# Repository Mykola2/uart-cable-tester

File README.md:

# RPi ↔ CUAV X7 telemetry cable tester

A production tester for the harness that runs from a Raspberry Pi 40-pin header to 3× JST-GH 6-pin (CUAV X7 TELEM1–3). Plug a cable in and get a PASS/FAIL verdict in under a second, with a colour per wire:

| Colour | Meaning |
|---|---|
| green | OK |
| red | open |
| orange | miswired (swapped, wrong cavity, wrong pin) |
| magenta | short |

A wiggle test catches intermittent crimps.

## How it works
- **Test lines.** Every contact on the 40-pin header and on the three JSTs (58 lines) has its own MCP23017 I/O pin, through a 220 Ω resistor. The header's power and GND pins are isolated test lines too.
- **Scan.** The RP2040 drives one line low at a time and reads all the others (a "walking one" scan). That builds the full connection map, which it compares to `wiring.json`.
- **Changing the pinout** needs no new hardware. Either edit `wiring.json` on the board's USB drive, or plug in a known-good cable and hold the button for 3 s (learn mode).
- **Ground wires** may land on any Pi GND pin, because the Pi's grounds are common.

## Layout
| Path | Contents |
|---|---|
| `firmware/` | CircuitPython firmware and PC simulation tests. See [firmware/README.md](firmware/README.md). |
| `hardware/` | KiCad 9 project, generator and check scripts, BOM. See [hardware/README.md](hardware/README.md). |
| `hardware/fab/` | JLCPCB order files: Gerber zip, `BOM_JLC.csv`, `CPL_JLC.csv`. |

## Quick commands
```bash
python firmware/pc_tests/test_tester.py      # firmware logic tests
python hardware/check_design.py              # netlist vs firmware pin map
python hardware/make_jlc.py                  # regenerate JLCPCB files from the board
```

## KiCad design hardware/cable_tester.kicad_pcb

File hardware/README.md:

# Cable tester PCB (KiCad 9)

`design.py` is the single source of truth: parts, footprints, pin-to-net map and positions.
Everything else is generated from it.

| File | What it is |
|---|---|
| `cable_tester.kicad_sch` | Schematic. Every pin is connected by a net label; opens normally in KiCad. |
| `cable_tester.kicad_pcb` | Board, 135×90 mm, 2 layers. Routed with Freerouting, GND pours on both layers. DRC is clean apart from silkscreen warnings. |
| `BOM.csv` | Grouped BOM with MPNs. `fab/BOM_JLC.csv` has the verified LCSC numbers. |
| `fab/` | JLCPCB files (Gerber zip, BOM, CPL), regenerated by `make_jlc.py`. |
| `move_decoupling.py` | One-off fix already applied to the routed board: moved C1–C4 next to the MCP23017 VDD pins. |
| `cable_tester_schematic.pdf`, `render_top.png`, `render_bottom.png` | Previews of the schematic and the board. |

## Regenerate

```bash
python gen_schematic.py
"C:/Program Files/KiCad/9.0/bin/kicad-cli.exe" sch erc cable_tester.kicad_sch
"C:/Program Files/KiCad/9.0/bin/kicad-cli.exe" sch export netlist --format kicadsexpr -o cable_tester.net cable_tester.kicad_sch
python check_design.py
"C:/Program Files/KiCad/9.0/bin/python.exe" gen_pcb.py
```

`check_design.py` checks the exported netlist against `firmware/hwmap.py`:
- each of the 58 test lines runs connector pin → 220 Ω → the MCP23017 pin the firmware expects
- the address straps are correct
- no DUT pin touches a power net

**The board is routed, so don't run `gen_pcb.py` again**, because it overwrites the board.
After that, make changes in the schematic (or `design.py` followed by `gen_schematic.py`), then use *Tools → Update PCB from Schematic* (F8).

## Circuit summary
- **A1**: Raspberry Pi Pico or a WeAct RP2040 (USB-C, same pinout).
  - USB supplies VBUS (+5 V), which powers the LEDs and buzzer.
  - The module's 3V3 output powers the MCP23017s.
  - Pins used: GP4 SDA, GP5 SCL, GP14 buzzer, GP15 button, GP16 LED data.
- **U1–U4**: MCP23017 at I²C addresses 0x20–0x23. Every DUT contact goes to its own expander pin through one resistor in RN1–RN15 (4×220 Ω arrays).
  - U1: H1–16. U2: H17–32. U3: GPA = H33–40, GPB0–5 = TELEM1.
  - U4: GPA0–5 = TELEM2, GPB0–5 = TELEM3.
  - Spare lines: U3 GPB6–7, U4 GPA6–7, U4 GPB6–7.
- **J1**: the 40-pin header. **None of its pins touch GND, 3V3 or 5V.** Each one is an isolated test line, which is why any future pinout can be tested with a config change only.
- **D1–D10**: WS2812B, driven through U5 (74AHCT1G125) to shift the data line from 3.3 V to 5 V.
  - D1–D9 are the wire LEDs: TX / RX / GND for each TELEM connector.
  - D10 is the PASS/FAIL status LED.
- **BZ1**: 5 V active buzzer, switched by Q1 with flyback diode D11.
- **SW1**: START / LEARN button.
- **J5**: optional SSD1306 OLED header. The firmware doesn't drive it yet.

## Before ordering
1. **Route it.** Freerouting works well:
   - export with *File → Export → Specctra DSN*, route in Freerouting, then import the `.ses` file
   - press **B** to fill the GND pours
   - run DRC
2. **Check JST orientation in the 3D viewer (Alt+3).** The TELEM connectors must open toward the bottom board edge.
3. **Check the header orientation.** It copies a Pi seen from above: pin 1 is bottom-left on the silkscreen, and the even-pin row is along the board edge. The cable must plug in exactly as it does on the Pi.
4. **Check the module footprint.** If you use a Pico clone, confirm it matches `RaspberryPi_Pico_SMD_HandSolder`.
5. **JST-GH receptacles are consumables.** They are rated for only ~50 mating cycles. Order spares and replace them with hot air when mating gets loose.

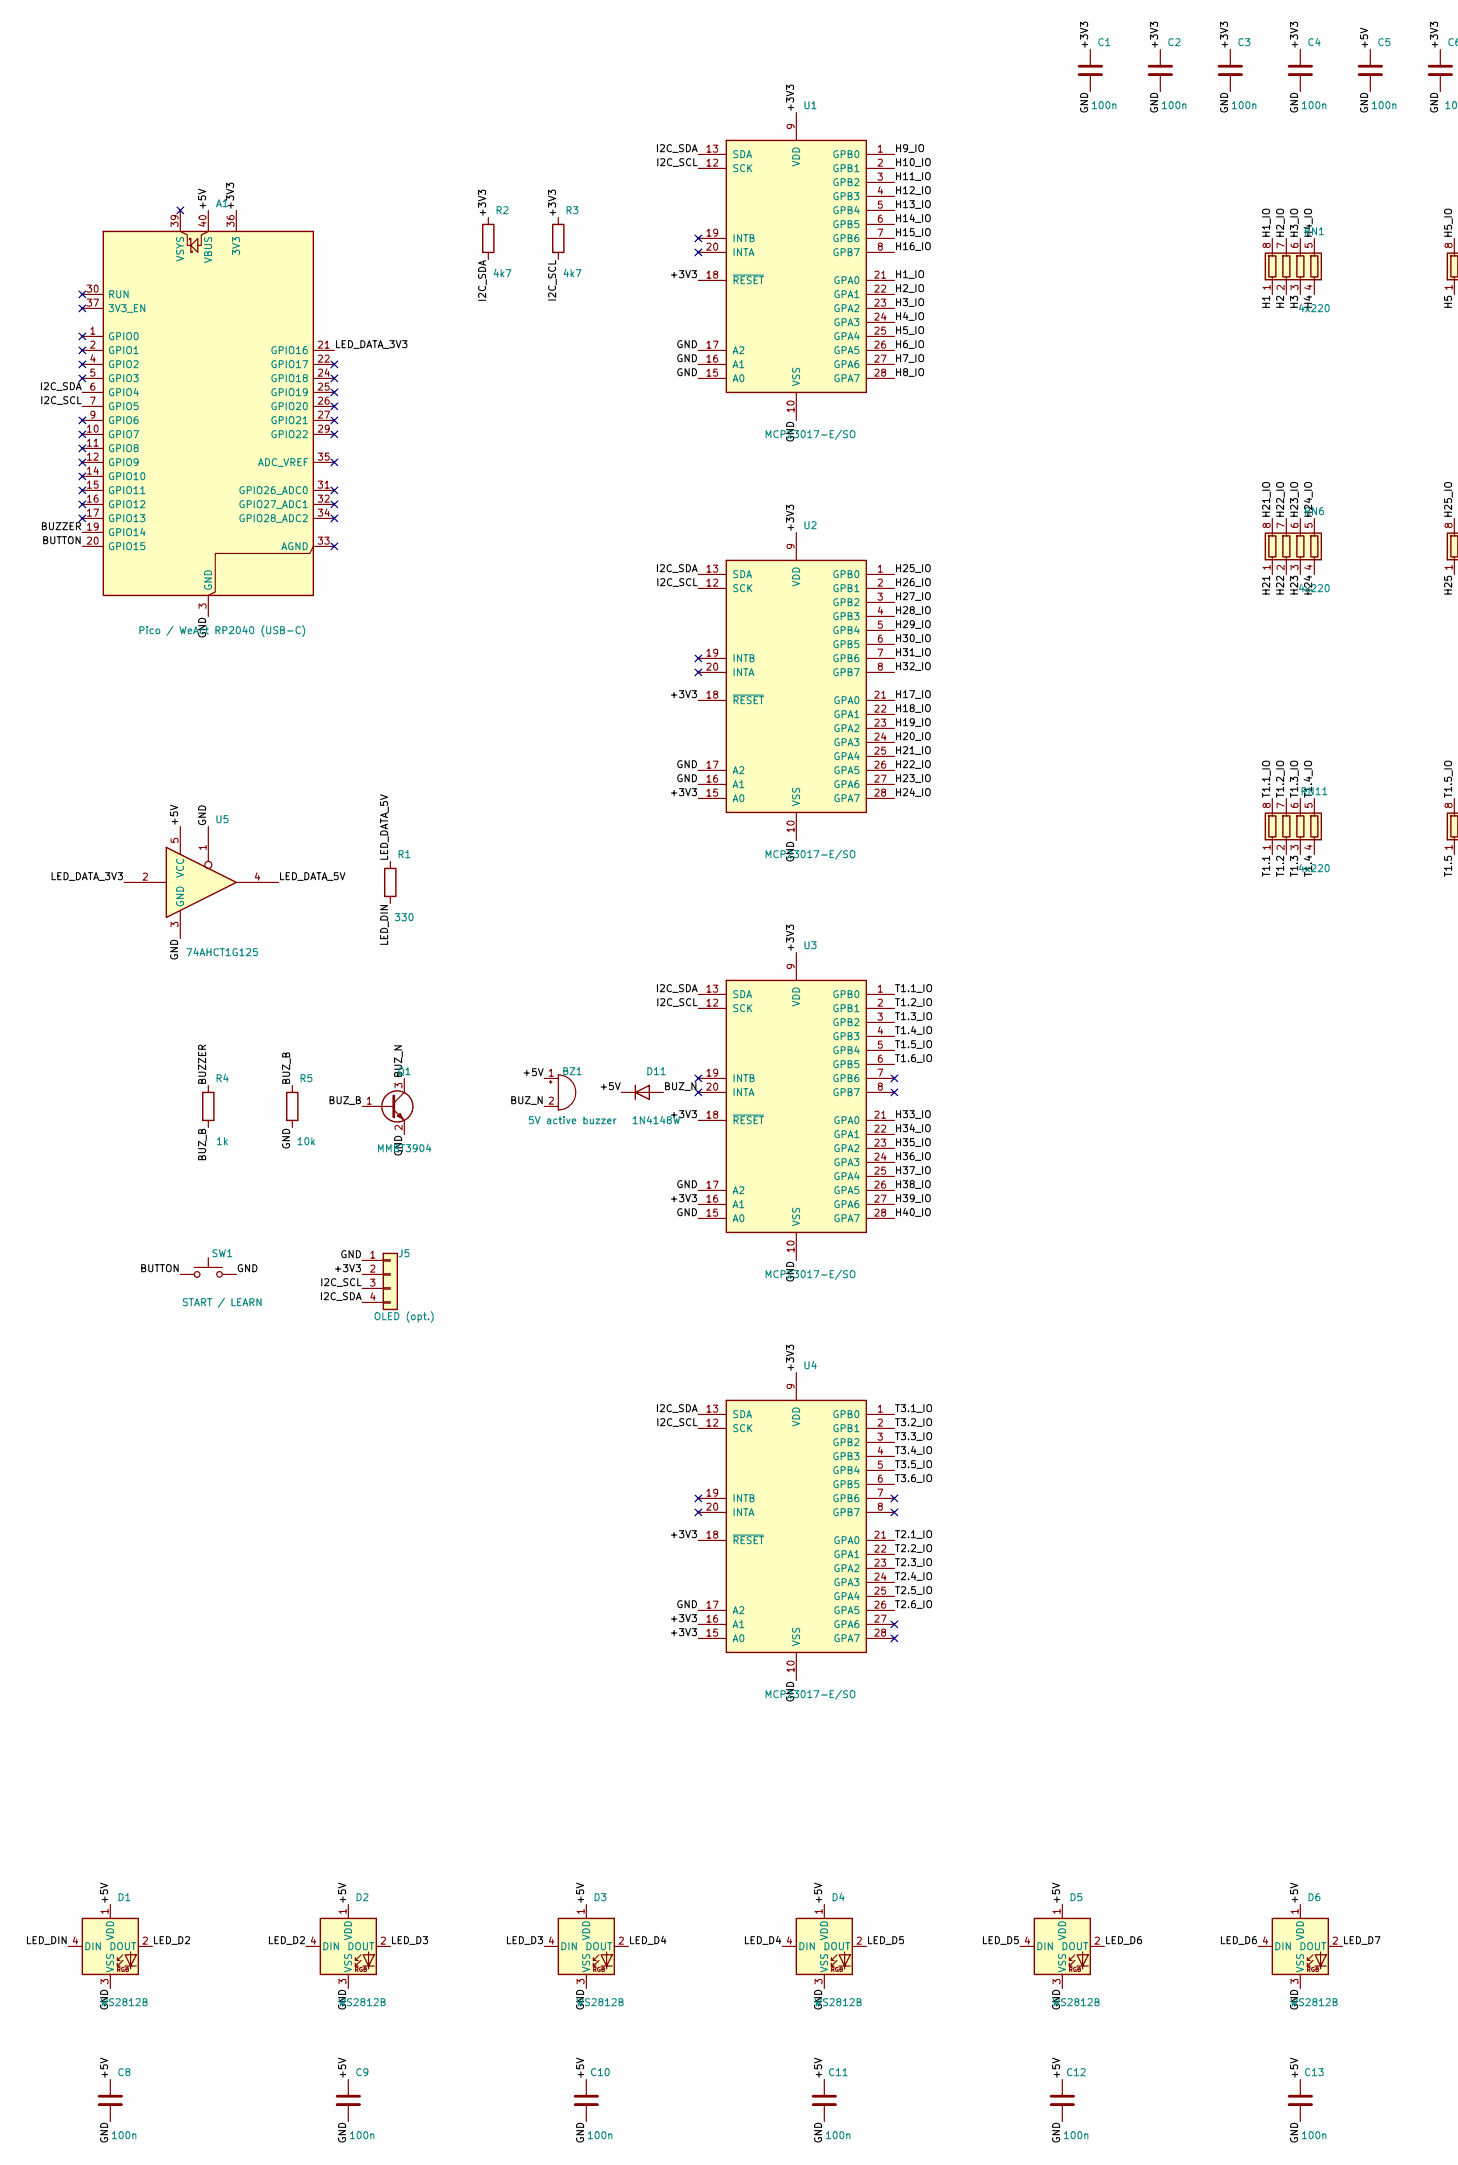
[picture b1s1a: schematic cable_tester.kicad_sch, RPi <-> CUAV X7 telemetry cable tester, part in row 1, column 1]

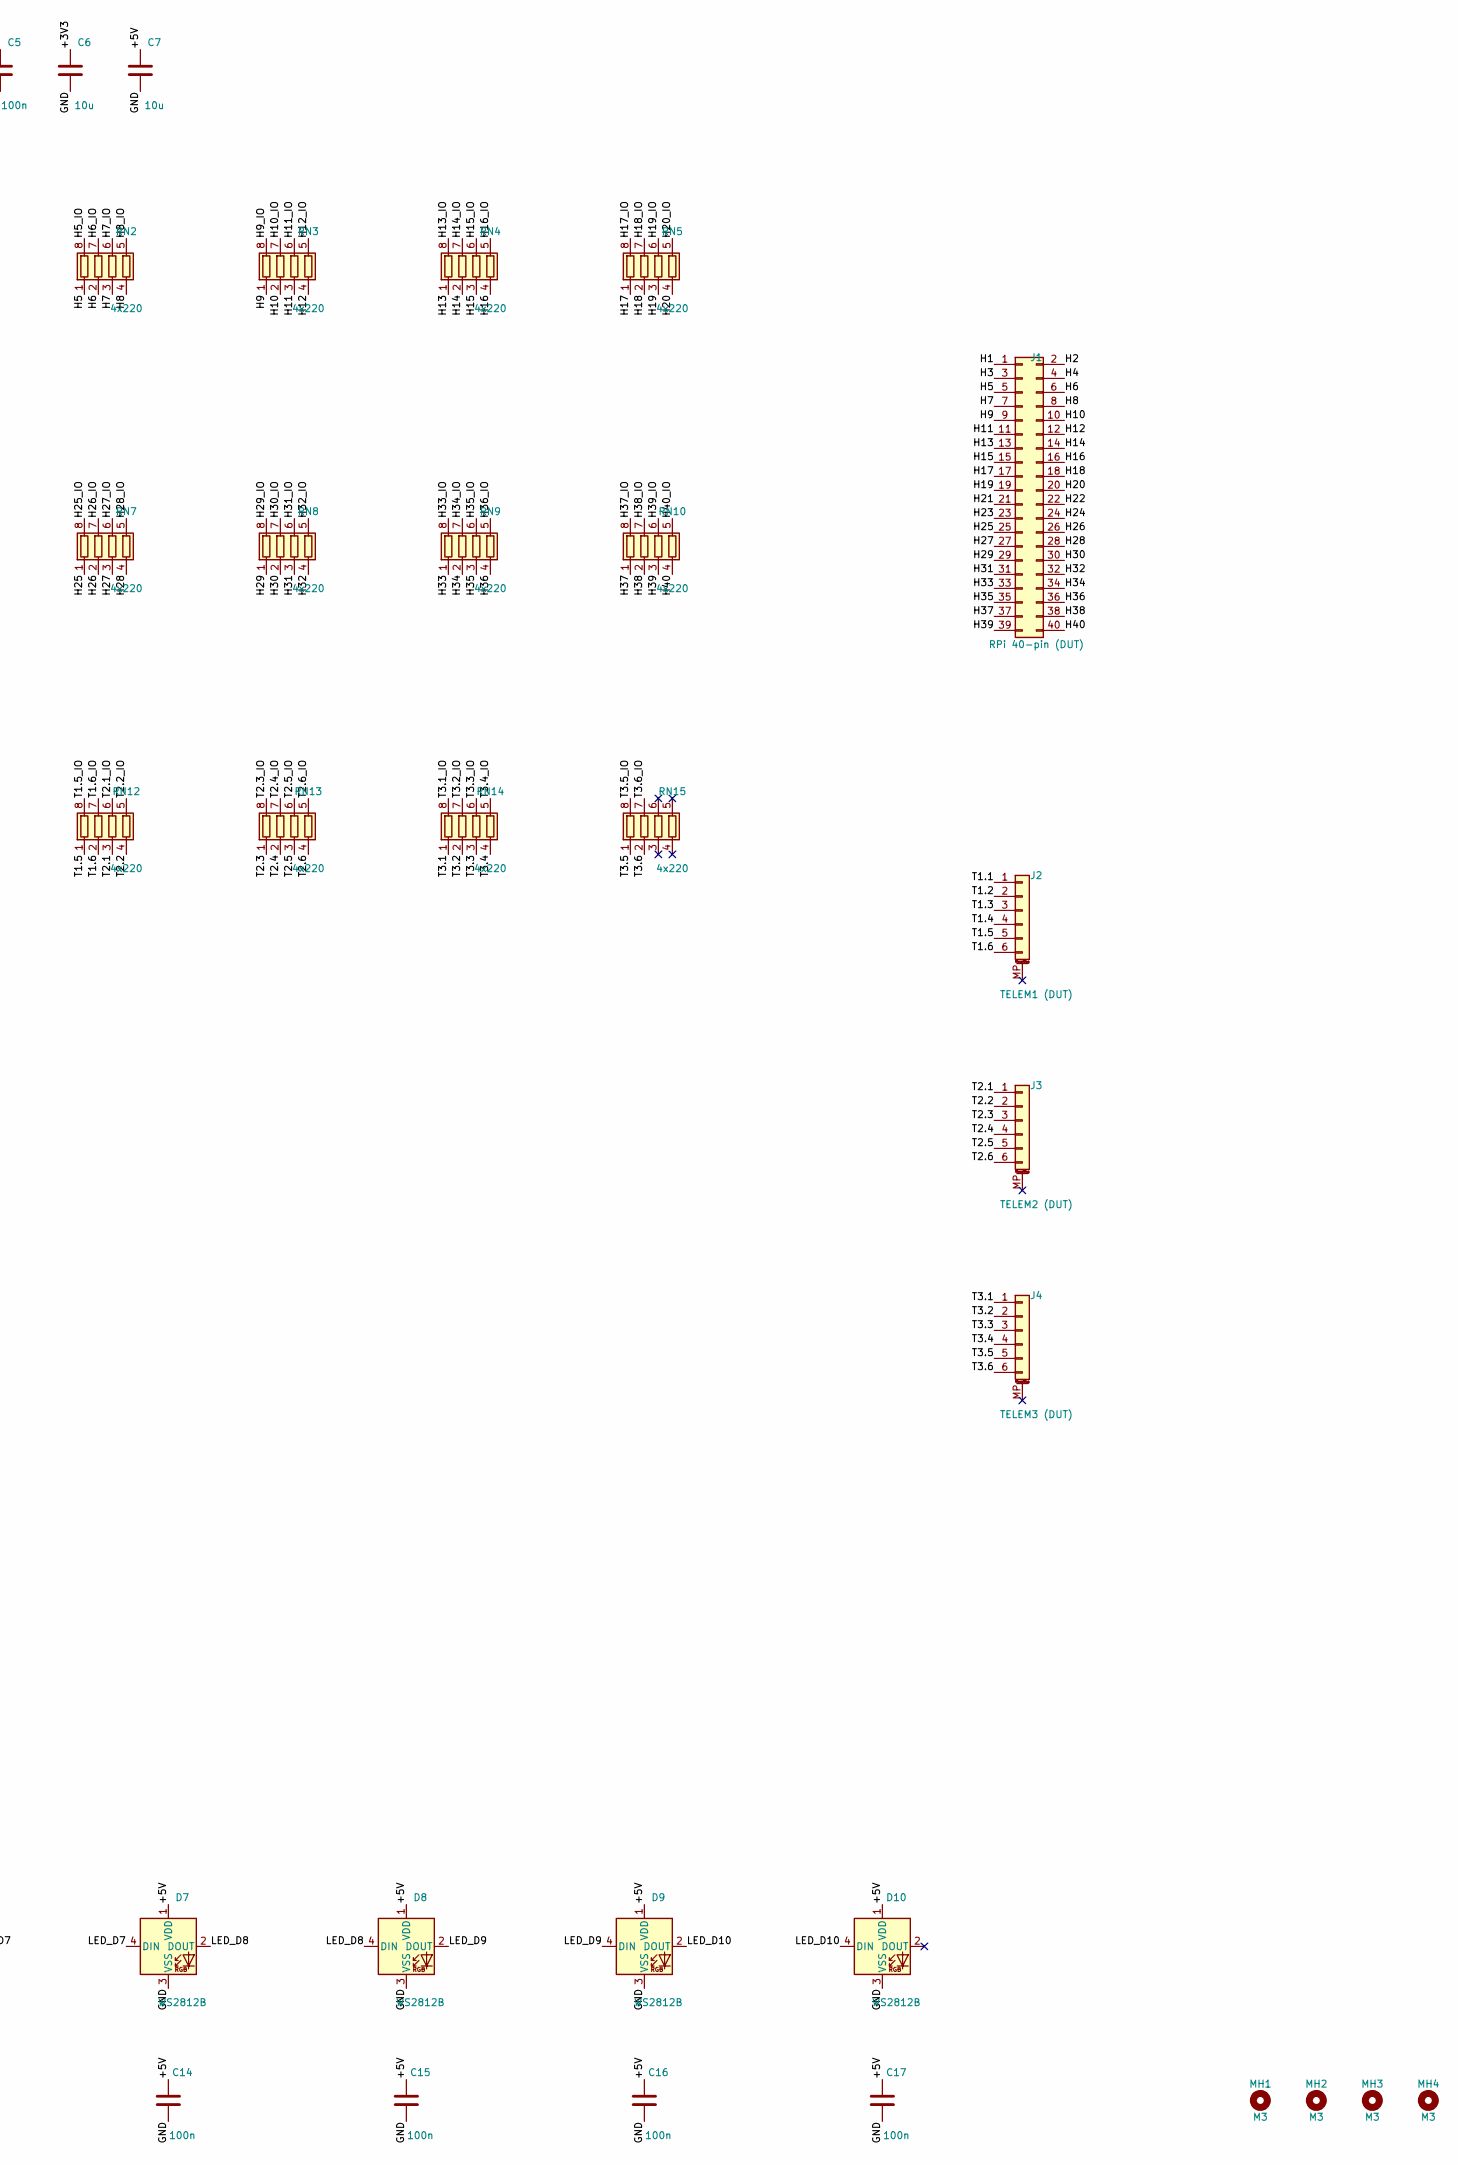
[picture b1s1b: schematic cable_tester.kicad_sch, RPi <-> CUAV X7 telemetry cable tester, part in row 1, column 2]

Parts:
A1: Pico / WeAct RP2040 (USB-C); RaspberryPi_Pico_SMD_HandSolder; MPN Raspberry Pi Pico (SC0915) or WeAct Stu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
BZ1: 5V active buzzer; Buzzer_12x9.5RM7.6; MPN TMB12A05 (12mm 5V active, 7.6mm pitch)
C1, C2, C3, C4, C5, C8, C9, C10, C11, C12, C13, C14, C15, C16, C17: 100n; C_0603_1608Metric; MPN 0603 100nF X7R 16V
C6, C7: 10u; C_0805_2012Metric; MPN 0805 10uF X5R 16V
D1, D2, D3, D4, D5, D6, D7, D8, D9, D10: WS2812B; LED_WS2812B_PLCC4_5.0x5.0mm_P3.2mm; MPN WS2812B-5050
D11: 1N4148W; D_SOD-123; MPN 1N4148W
J1: RPi 40-pin (DUT); PinHeader_2x20_P2.54mm_Vertical; MPN 2x20 2.54mm male pin header
J2: TELEM1 (DUT); JST_GH_SM06B-GHS-TB_1x06-1MP_P1.25mm_Horizontal; MPN JST SM06B-GHS-TB(LF)(SN)
J3: TELEM2 (DUT); JST_GH_SM06B-GHS-TB_1x06-1MP_P1.25mm_Horizontal; MPN JST SM06B-GHS-TB(LF)(SN)
J4: TELEM3 (DUT); JST_GH_SM06B-GHS-TB_1x06-1MP_P1.25mm_Horizontal; MPN JST SM06B-GHS-TB(LF)(SN)
J5: OLED (opt.); PinHeader_1x04_P2.54mm_Vertical; MPN 1x4 2.54mm header (DNP)
MH1, MH2, MH3, MH4: M3; MountingHole_3.2mm_M3; MPN (none)
Q1: MMBT3904; SOT-23; MPN MMBT3904
R1: 330; R_0603_1608Metric; MPN 0603 330R
R2, R3: 4k7; R_0603_1608Metric; MPN 0603 4.7k
R4: 1k; R_0603_1608Metric; MPN 0603 1k
R5: 10k; R_0603_1608Metric; MPN 0603 10k
RN1, RN2, RN3, RN4, RN5, RN6, RN7, RN8, RN9, RN10, RN11, RN12, RN13, RN14, RN15: 4x220; R_Array_Convex_4x0603; MPN YC164-JR-07220RL (4x220R 0603 convex)
SW1: START / LEARN; SW_PUSH_6mm_H5mm; MPN 6x6mm THT tactile switch
U1, U2, U3, U4: MCP23017-E/SO; SOIC-28W_7.5x17.9mm_P1.27mm; MPN MCP23017-E/SO
U5: 74AHCT1G125; SOT-23-5; MPN SN74AHCT1G125DBVR

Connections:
/+3V3: A1.36 (3V3), C1.1, C2.1, C3.1, C4.1, C6.1, J5.2, R2.1, R3.1, U1.9 (VDD), U1.18 (~RESET), U2.9 (VDD), U2.15 (A0), U2.18 (~RESET), U3.9 (VDD), U3.16 (A1), U3.18 (~RESET), U4.9 (VDD), U4.15 (A0), U4.16 (A1), U4.18 (~RESET)
/+5V: A1.40 (VBUS), BZ1.1 (+), C5.1, C7.1, C8.1, C9.1, C10.1, C11.1, C12.1, C13.1, C14.1, C15.1, C16.1, C17.1, D1.1 (VDD), D2.1 (VDD), D3.1 (VDD), D4.1 (VDD), D5.1 (VDD), D6.1 (VDD), D7.1 (VDD), D8.1 (VDD), D9.1 (VDD), D10.1 (VDD), D11.1 (K), U5.5 (VCC)
/BUTTON: A1.20 (GPIO15), SW1.1
/BUZZER: A1.19 (GPIO14), R4.1
/BUZ_B: Q1.1 (B), R4.2, R5.1
/BUZ_N: BZ1.2 (-), D11.2 (A), Q1.3 (C)
/GND: A1.3 (GND), A1.8 (GND), A1.13 (GND), A1.18 (GND), A1.23 (GND), A1.28 (GND), A1.38 (GND), C1.2, C2.2, C3.2, C4.2, C5.2, C6.2, C7.2, C8.2, C9.2, C10.2, C11.2, C12.2, C13.2, C14.2, C15.2, C16.2, C17.2, D1.3 (VSS), D2.3 (VSS), D3.3 (VSS), D4.3 (VSS), D5.3 (VSS), D6.3 (VSS), D7.3 (VSS), D8.3 (VSS), D9.3 (VSS), D10.3 (VSS), J5.1, Q1.2 (E), R5.2, SW1.2, U1.10 (VSS), U1.15 (A0), U1.16 (A1), U1.17 (A2), U2.10 (VSS), U2.16 (A1), U2.17 (A2), U3.10 (VSS), U3.15 (A0), U3.17 (A2), U4.10 (VSS), U4.17 (A2), U5.1, U5.3 (GND)
/H1: J1.1, RN1.1 (R1.1)
/H1_IO: RN1.8 (R1.2), U1.21 (GPA0)
/H2: J1.2, RN1.2 (R2.1)
/H2_IO: RN1.7 (R2.2), U1.22 (GPA1)
/H3: J1.3, RN1.3 (R3.1)
/H3_IO: RN1.6 (R3.2), U1.23 (GPA2)
/H4: J1.4, RN1.4 (R4.1)
/H4_IO: RN1.5 (R4.2), U1.24 (GPA3)
/H5: J1.5, RN2.1 (R1.1)
/H5_IO: RN2.8 (R1.2), U1.25 (GPA4)
/H6: J1.6, RN2.2 (R2.1)
/H6_IO: RN2.7 (R2.2), U1.26 (GPA5)
/H7: J1.7, RN2.3 (R3.1)
/H7_IO: RN2.6 (R3.2), U1.27 (GPA6)
/H8: J1.8, RN2.4 (R4.1)
/H8_IO: RN2.5 (R4.2), U1.28 (GPA7)
/H9: J1.9, RN3.1 (R1.1)
/H9_IO: RN3.8 (R1.2), U1.1 (GPB0)
/H10: J1.10, RN3.2 (R2.1)
/H10_IO: RN3.7 (R2.2), U1.2 (GPB1)
/H11: J1.11, RN3.3 (R3.1)
/H11_IO: RN3.6 (R3.2), U1.3 (GPB2)
/H12: J1.12, RN3.4 (R4.1)
/H12_IO: RN3.5 (R4.2), U1.4 (GPB3)
/H13: J1.13, RN4.1 (R1.1)
/H13_IO: RN4.8 (R1.2), U1.5 (GPB4)
/H14: J1.14, RN4.2 (R2.1)
/H14_IO: RN4.7 (R2.2), U1.6 (GPB5)
/H15: J1.15, RN4.3 (R3.1)
/H15_IO: RN4.6 (R3.2), U1.7 (GPB6)
/H16: J1.16, RN4.4 (R4.1)
/H16_IO: RN4.5 (R4.2), U1.8 (GPB7)
/H17: J1.17, RN5.1 (R1.1)
/H17_IO: RN5.8 (R1.2), U2.21 (GPA0)
/H18: J1.18, RN5.2 (R2.1)
/H18_IO: RN5.7 (R2.2), U2.22 (GPA1)
/H19: J1.19, RN5.3 (R3.1)
/H19_IO: RN5.6 (R3.2), U2.23 (GPA2)
/H20: J1.20, RN5.4 (R4.1)
/H20_IO: RN5.5 (R4.2), U2.24 (GPA3)
/H21: J1.21, RN6.1 (R1.1)
/H21_IO: RN6.8 (R1.2), U2.25 (GPA4)
/H22: J1.22, RN6.2 (R2.1)
/H22_IO: RN6.7 (R2.2), U2.26 (GPA5)
/H23: J1.23, RN6.3 (R3.1)
/H23_IO: RN6.6 (R3.2), U2.27 (GPA6)
/H24: J1.24, RN6.4 (R4.1)
/H24_IO: RN6.5 (R4.2), U2.28 (GPA7)
/H25: J1.25, RN7.1 (R1.1)
/H25_IO: RN7.8 (R1.2), U2.1 (GPB0)
/H26: J1.26, RN7.2 (R2.1)
/H26_IO: RN7.7 (R2.2), U2.2 (GPB1)
/H27: J1.27, RN7.3 (R3.1)
/H27_IO: RN7.6 (R3.2), U2.3 (GPB2)
/H28: J1.28, RN7.4 (R4.1)
/H28_IO: RN7.5 (R4.2), U2.4 (GPB3)
/H29: J1.29, RN8.1 (R1.1)
/H29_IO: RN8.8 (R1.2), U2.5 (GPB4)
/H30: J1.30, RN8.2 (R2.1)
/H30_IO: RN8.7 (R2.2), U2.6 (GPB5)
/H31: J1.31, RN8.3 (R3.1)
/H31_IO: RN8.6 (R3.2), U2.7 (GPB6)
/H32: J1.32, RN8.4 (R4.1)
/H32_IO: RN8.5 (R4.2), U2.8 (GPB7)
/H33: J1.33, RN9.1 (R1.1)
/H33_IO: RN9.8 (R1.2), U3.21 (GPA0)
/H34: J1.34, RN9.2 (R2.1)
/H34_IO: RN9.7 (R2.2), U3.22 (GPA1)
/H35: J1.35, RN9.3 (R3.1)
/H35_IO: RN9.6 (R3.2), U3.23 (GPA2)
/H36: J1.36, RN9.4 (R4.1)
/H36_IO: RN9.5 (R4.2), U3.24 (GPA3)
/H37: J1.37, RN10.1 (R1.1)
/H37_IO: RN10.8 (R1.2), U3.25 (GPA4)
/H38: J1.38, RN10.2 (R2.1)
/H38_IO: RN10.7 (R2.2), U3.26 (GPA5)
/H39: J1.39, RN10.3 (R3.1)
/H39_IO: RN10.6 (R3.2), U3.27 (GPA6)
/H40: J1.40, RN10.4 (R4.1)
/H40_IO: RN10.5 (R4.2), U3.28 (GPA7)
/I2C_SCL: A1.7 (GPIO5), J5.3, R3.2, U1.12 (SCK), U2.12 (SCK), U3.12 (SCK), U4.12 (SCK)
/I2C_SDA: A1.6 (GPIO4), J5.4, R2.2, U1.13 (SDA), U2.13 (SDA), U3.13 (SDA), U4.13 (SDA)
/LED_D2: D1.2 (DOUT), D2.4 (DIN)
/LED_D3: D2.2 (DOUT), D3.4 (DIN)
/LED_D4: D3.2 (DOUT), D4.4 (DIN)
/LED_D5: D4.2 (DOUT), D5.4 (DIN)
/LED_D6: D5.2 (DOUT), D6.4 (DIN)
/LED_D7: D6.2 (DOUT), D7.4 (DIN)
/LED_D8: D7.2 (DOUT), D8.4 (DIN)
/LED_D9: D8.2 (DOUT), D9.4 (DIN)
/LED_D10: D9.2 (DOUT), D10.4 (DIN)
/LED_DATA_3V3: A1.21 (GPIO16), U5.2
/LED_DATA_5V: R1.1, U5.4
/LED_DIN: D1.4 (DIN), R1.2
/T1.1: J2.1, RN11.1 (R1.1)
/T1.1_IO: RN11.8 (R1.2), U3.1 (GPB0)
/T1.2: J2.2, RN11.2 (R2.1)
/T1.2_IO: RN11.7 (R2.2), U3.2 (GPB1)
/T1.3: J2.3, RN11.3 (R3.1)
/T1.3_IO: RN11.6 (R3.2), U3.3 (GPB2)
/T1.4: J2.4, RN11.4 (R4.1)
/T1.4_IO: RN11.5 (R4.2), U3.4 (GPB3)
/T1.5: J2.5, RN12.1 (R1.1)
/T1.5_IO: RN12.8 (R1.2), U3.5 (GPB4)
/T1.6: J2.6, RN12.2 (R2.1)
/T1.6_IO: RN12.7 (R2.2), U3.6 (GPB5)
/T2.1: J3.1, RN12.3 (R3.1)
/T2.1_IO: RN12.6 (R3.2), U4.21 (GPA0)
/T2.2: J3.2, RN12.4 (R4.1)
/T2.2_IO: RN12.5 (R4.2), U4.22 (GPA1)
/T2.3: J3.3, RN13.1 (R1.1)
/T2.3_IO: RN13.8 (R1.2), U4.23 (GPA2)
/T2.4: J3.4, RN13.2 (R2.1)
/T2.4_IO: RN13.7 (R2.2), U4.24 (GPA3)
/T2.5: J3.5, RN13.3 (R3.1)
/T2.5_IO: RN13.6 (R3.2), U4.25 (GPA4)
/T2.6: J3.6, RN13.4 (R4.1)
/T2.6_IO: RN13.5 (R4.2), U4.26 (GPA5)
/T3.1: J4.1, RN14.1 (R1.1)
/T3.1_IO: RN14.8 (R1.2), U4.1 (GPB0)
/T3.2: J4.2, RN14.2 (R2.1)
/T3.2_IO: RN14.7 (R2.2), U4.2 (GPB1)
/T3.3: J4.3, RN14.3 (R3.1)
/T3.3_IO: RN14.6 (R3.2), U4.3 (GPB2)
/T3.4: J4.4, RN14.4 (R4.1)
/T3.4_IO: RN14.5 (R4.2), U4.4 (GPB3)
/T3.5: J4.5, RN15.1 (R1.1)
/T3.5_IO: RN15.8 (R1.2), U4.5 (GPB4)
/T3.6: J4.6, RN15.2 (R2.1)
/T3.6_IO: RN15.7 (R2.2), U4.6 (GPB5)

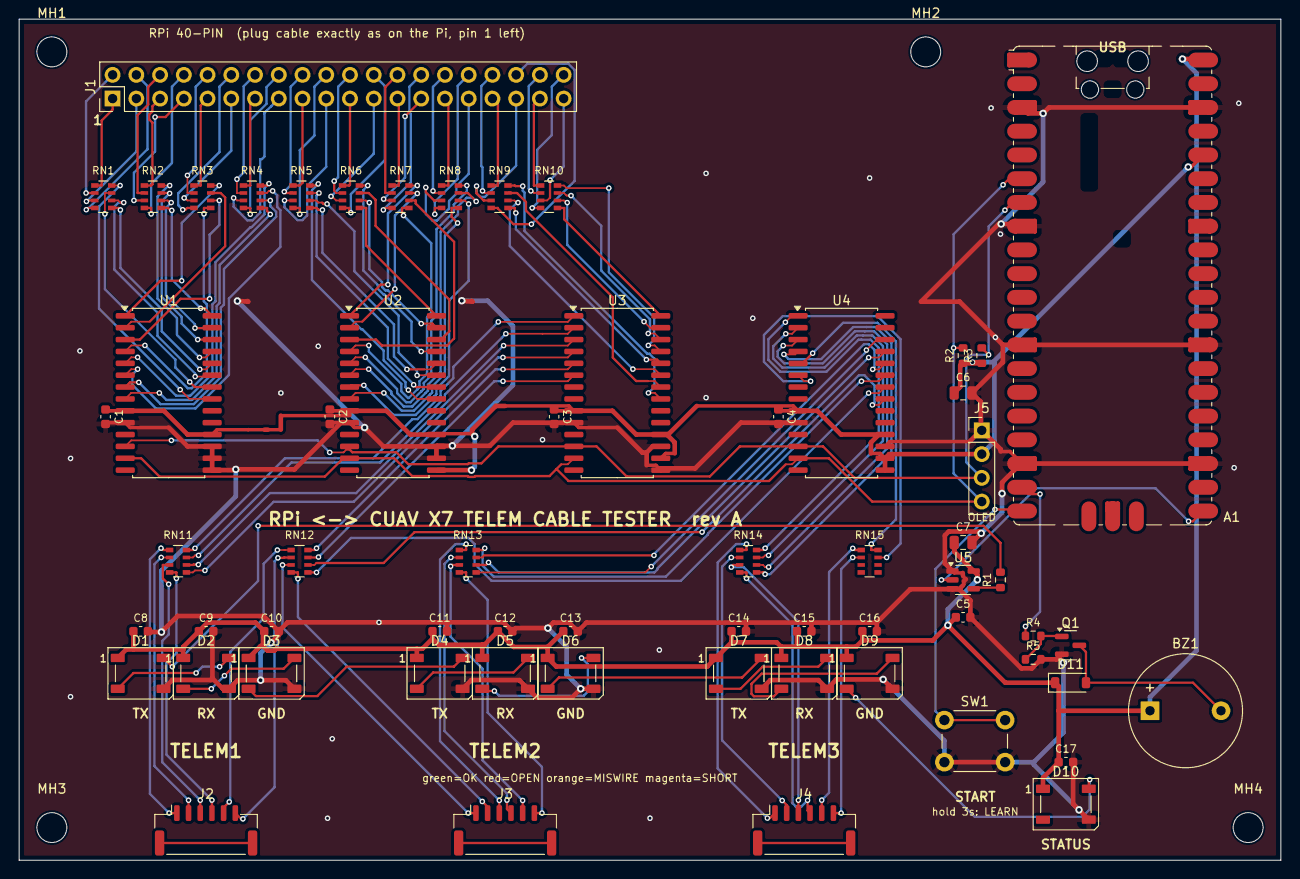
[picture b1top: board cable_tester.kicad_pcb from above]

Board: 2 copper layers, 135.0 x 90.0 mm, 66 parts (0 on the bottom side), 137 nets.

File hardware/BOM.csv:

Qty,References,Value,Footprint,MPN,LCSC (fill in),Notes
1,"A1","Pico / WeAct RP2040 (USB-C)","Module:RaspberryPi_Pico_SMD_HandSolder","Raspberry Pi Pico (SC0915) or WeAct Studio RP2040",,"USB-C variant recommended; castellated, solder directly or on 2x 1x20 sockets"
1,"BZ1","5V active buzzer","Buzzer_Beeper:Buzzer_12x9.5RM7.6","TMB12A05 (12mm 5V active, 7.6mm pitch)",,""
15,"C1 C2 C3 C4 C5 C8 C9 C10 C11 C12 C13 C14 C15 C16 C17","100n","Capacitor_SMD:C_0603_1608Metric","0603 100nF X7R 16V",,""
2,"C6 C7","10u","Capacitor_SMD:C_0805_2012Metric","0805 10uF X5R 16V",,""
10,"D1 D2 D3 D4 D5 D6 D7 D8 D9 D10","WS2812B","LED_SMD:LED_WS2812B_PLCC4_5.0x5.0mm_P3.2mm","WS2812B-5050",,""
1,"D11","1N4148W","Diode_SMD:D_SOD-123","1N4148W",,""
1,"J1","RPi 40-pin (DUT)","Connector_PinHeader_2.54mm:PinHeader_2x20_P2.54mm_Vertical","2x20 2.54mm male pin header",,"ALL pins are isolated test lines - never tie to power/GND"
1,"J2","TELEM1 (DUT)","Connector_JST:JST_GH_SM06B-GHS-TB_1x06-1MP_P1.25mm_Horizontal","JST SM06B-GHS-TB(LF)(SN)",,"~50 mating cycles: consumable, keep spares"
1,"J3","TELEM2 (DUT)","Connector_JST:JST_GH_SM06B-GHS-TB_1x06-1MP_P1.25mm_Horizontal","JST SM06B-GHS-TB(LF)(SN)",,"~50 mating cycles: consumable, keep spares"
1,"J4","TELEM3 (DUT)","Connector_JST:JST_GH_SM06B-GHS-TB_1x06-1MP_P1.25mm_Horizontal","JST SM06B-GHS-TB(LF)(SN)",,"~50 mating cycles: consumable, keep spares"
1,"J5","OLED (opt.)","Connector_PinHeader_2.54mm:PinHeader_1x04_P2.54mm_Vertical","1x4 2.54mm header (DNP)",,"SSD1306 128x64 I2C, GND-VCC-SCL-SDA"
1,"Q1","MMBT3904","Package_TO_SOT_SMD:SOT-23","MMBT3904",,""
1,"R1","330","Resistor_SMD:R_0603_1608Metric","0603 330R",,""
2,"R2 R3","4k7","Resistor_SMD:R_0603_1608Metric","0603 4.7k",,""
1,"R4","1k","Resistor_SMD:R_0603_1608Metric","0603 1k",,""
1,"R5","10k","Resistor_SMD:R_0603_1608Metric","0603 10k",,""
15,"RN1 RN2 RN3 RN4 RN5 RN6 RN7 RN8 RN9 RN10 RN11 RN12 RN13 RN14 RN15","4x220","Resistor_SMD:R_Array_Convex_4x0603","YC164-JR-07220RL (4x220R 0603 convex)",,""
1,"SW1","START / LEARN","Button_Switch_THT:SW_PUSH_6mm_H5mm","6x6mm THT tactile switch",,"short press: retest / force verdict; hold 3s: learn"
4,"U1 U2 U3 U4","MCP23017-E/SO","Package_SO:SOIC-28W_7.5x17.9mm_P1.27mm","MCP23017-E/SO",,"I2C addr 0x20; I2C addr 0x21; I2C addr 0x22; I2C addr 0x23"
1,"U5","74AHCT1G125","Package_TO_SOT_SMD:SOT-23-5","SN74AHCT1G125DBVR",,""

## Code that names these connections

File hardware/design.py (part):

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
Every component: KiCad symbol, footprint, pin -> net map, schematic position,
starter PCB position. gen_schematic.py and gen_pcb.py both read this file.
Pin keys may be a pin number ("21") or a pin name ("GPIO4"); pins not listed
get a no-connect flag.
"""

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# ---- MCU module ---------------------------------------------------------------
add("A1", "MCU_Module", "RaspberryPi_Pico", "Pico / WeAct RP2040 (USB-C)",
    "Module:RaspberryPi_Pico_SMD_HandSolder",
    {"GPIO4": "I2C_SDA", "GPIO5": "I2C_SCL", "GPIO14": "BUZZER", "GPIO15": "BUTTON",
     "GPIO16": "LED_DATA_3V3", "VBUS": "+5V", "3V3": "+3V3", "GND": "GND"},
    sch=(55.88, 88.9), pcb=(117.0, 28.5, 0, "F"),
    mpn="Raspberry Pi Pico (SC0915) or WeAct Studio RP2040",
    note="USB-C variant recommended; castellated, solder directly or on 2x 1x20 sockets")

# ---- I/O expanders --------------------------------------------------------------
for _i, _u in enumerate(("U1", "U2", "U3", "U4")):
    _pins = {"VDD": "+3V3", "VSS": "GND", "SCK": "I2C_SCL", "SDA": "I2C_SDA", "~{RESET}": "+3V3"}
    _pins.update(dict(zip(("A2", "A1", "A0"), MCP_ADDR_PINS[_u])))
    for _net, _ref, _pin in LINES:
        if _ref == _u:
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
